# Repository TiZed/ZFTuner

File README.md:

# ZFTuner

A 100W automatic antenna tuner, utilizing latching relays.

This project is still work in progress...

CC BY-NC-SA 4.0 Deed\
https://creativecommons.org/licenses/by-nc-sa/4.0/

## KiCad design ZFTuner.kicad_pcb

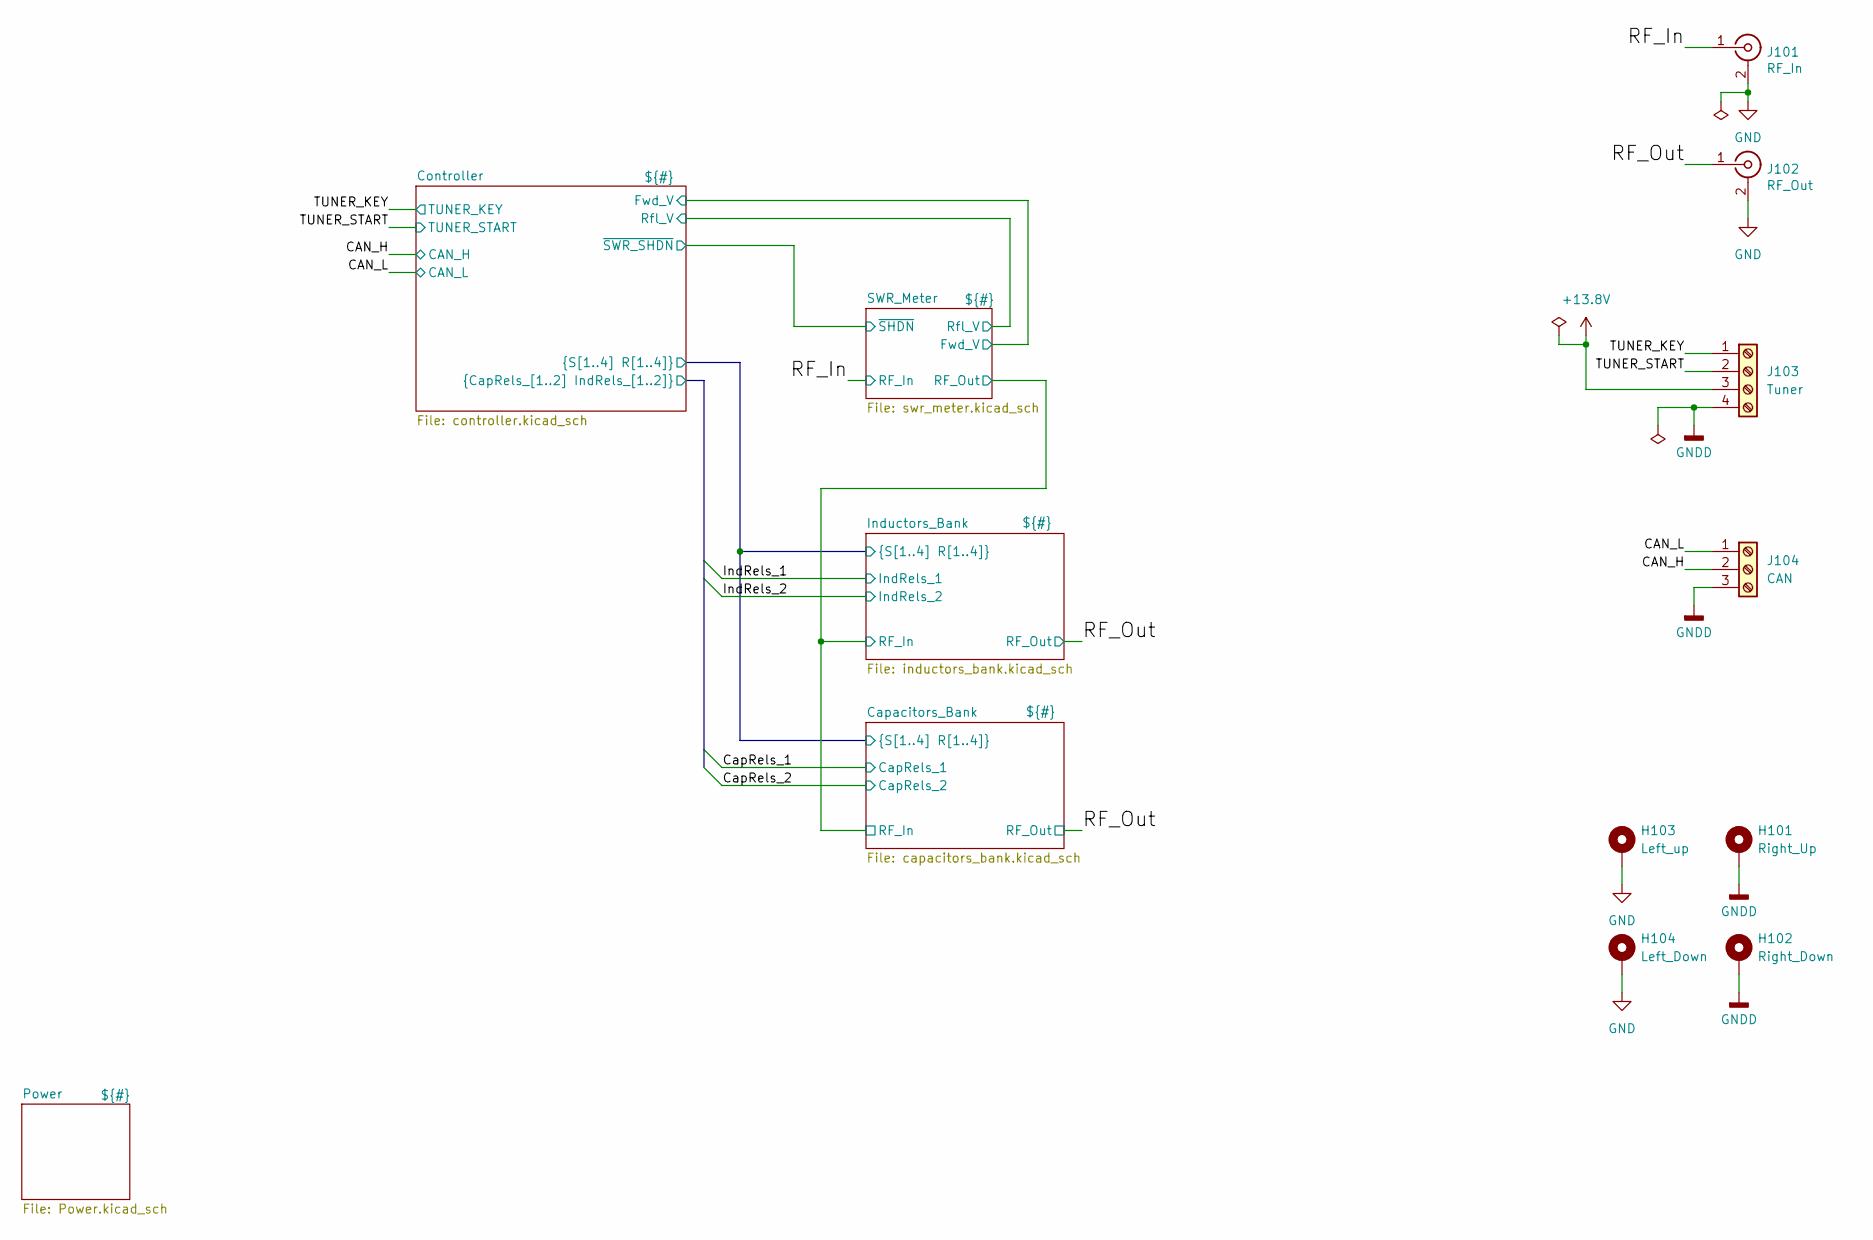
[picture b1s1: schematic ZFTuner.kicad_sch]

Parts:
H101: Right_Up; MountingHole_3.2mm_M3_ISO7380_Pad
H102: Right_Down; MountingHole_3.2mm_M3_ISO7380_Pad
H103: Left_up; MountingHole_3.2mm_M3_ISO7380_Pad
H104: Left_Down; MountingHole_3.2mm_M3_ISO7380_Pad
J101: RF_In; SMA_Bat_Wireless_BWSMA-KE-P001_EdgeMount_1.6mm-PCB
J102: RF_Out; SMA_Bat_Wireless_BWSMA-KE-P001_EdgeMount_1.6mm-PCB
J103: Tuner; TerminalBlock_Phoenix_PT-1,5-4-3.5-H_1x04_P3.50mm_Horizontal
J104: CAN; TerminalBlock_Phoenix_PT-1,5-3-3.5-H_1x03_P3.50mm_Horizontal

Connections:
+13.8V: J103.3; also elsewhere on the board
/CAN_H: J104.2; also elsewhere on the board
/CAN_L: J104.1; also elsewhere on the board
/RF_In: J101.1 (In); also elsewhere on the board
/RF_Out: J102.1 (In); also elsewhere on the board
/TUNER_KEY: J103.1; also elsewhere on the board
/TUNER_START: J103.2; also elsewhere on the board
GND: H103.1, H104.1, J101.2 (Ext), J102.2 (Ext); also elsewhere on the board
GNDD: H101.1, H102.1, J103.4, J104.3; also elsewhere on the board

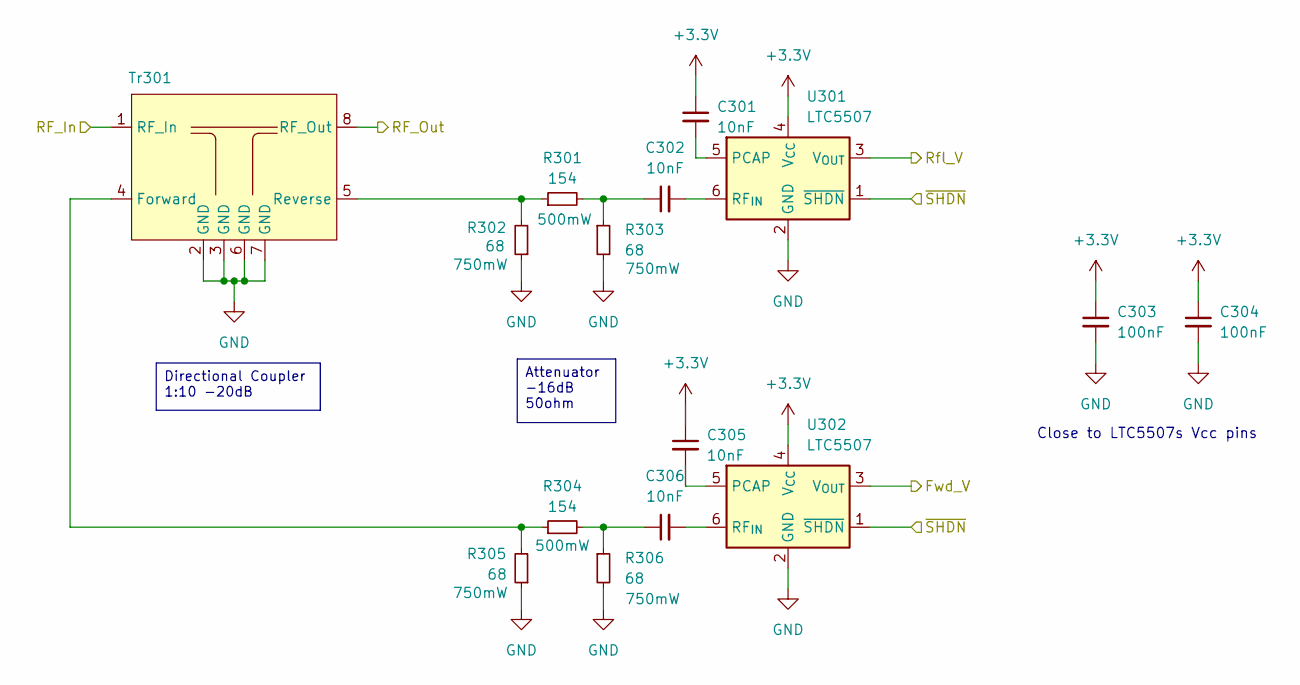
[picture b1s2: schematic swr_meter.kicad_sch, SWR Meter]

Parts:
C301, C302, C305, C306: 10nF; C_0603_1608Metric
C303, C304: 100nF; C_0603_1608Metric
R301, R304: 154; R_1210_3225Metric
R302, R303, R305, R306: 68; R_2010_5025Metric
Tr301: Direction_Coupler
U301, U302: LTC5507; TSOT-23-6

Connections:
+3.3V: C301.1, C303.1, C304.1, C305.1, U301.4 (V_{CC}), U302.4 (V_{CC}); also elsewhere on the board
/Capacitors_Bank/RF_In: Tr301.8 (RF_Out); also elsewhere on the board
/Controller/Fwd_V: U302.3 (V_{OUT}); also elsewhere on the board
/Controller/Rfl_V: U301.3 (V_{OUT}); also elsewhere on the board
/Controller/~SWR_SHDN: U301.1 (~SHDN), U302.1 (~SHDN); also elsewhere on the board
/RF_In: Tr301.1 (RF_In); also elsewhere on the board
GND: C303.2, C304.2, R302.1, R303.2, R305.1, R306.2, Tr301.2 (GND), Tr301.3 (GND), Tr301.6 (GND), Tr301.7 (GND), U301.2 (GND), U302.2 (GND); also elsewhere on the board
unnamed: C302.1, R301.2, R303.1
unnamed: C306.1, R304.2, R306.1
unnamed: R304.1, R305.2, Tr301.4 (Forward)
unnamed: R301.1, R302.2, Tr301.5 (Reverse)
unnamed: C301.2, U301.5 (PCAP)
unnamed: C302.2, U301.6 (RF_{IN})
unnamed: C305.2, U302.5 (PCAP)
unnamed: C306.2, U302.6 (RF_{IN})

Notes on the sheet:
Close to LTC5507s Vcc pins
Attenuator -16dB 50ohm
Directional Coupler 1:10 -20dB

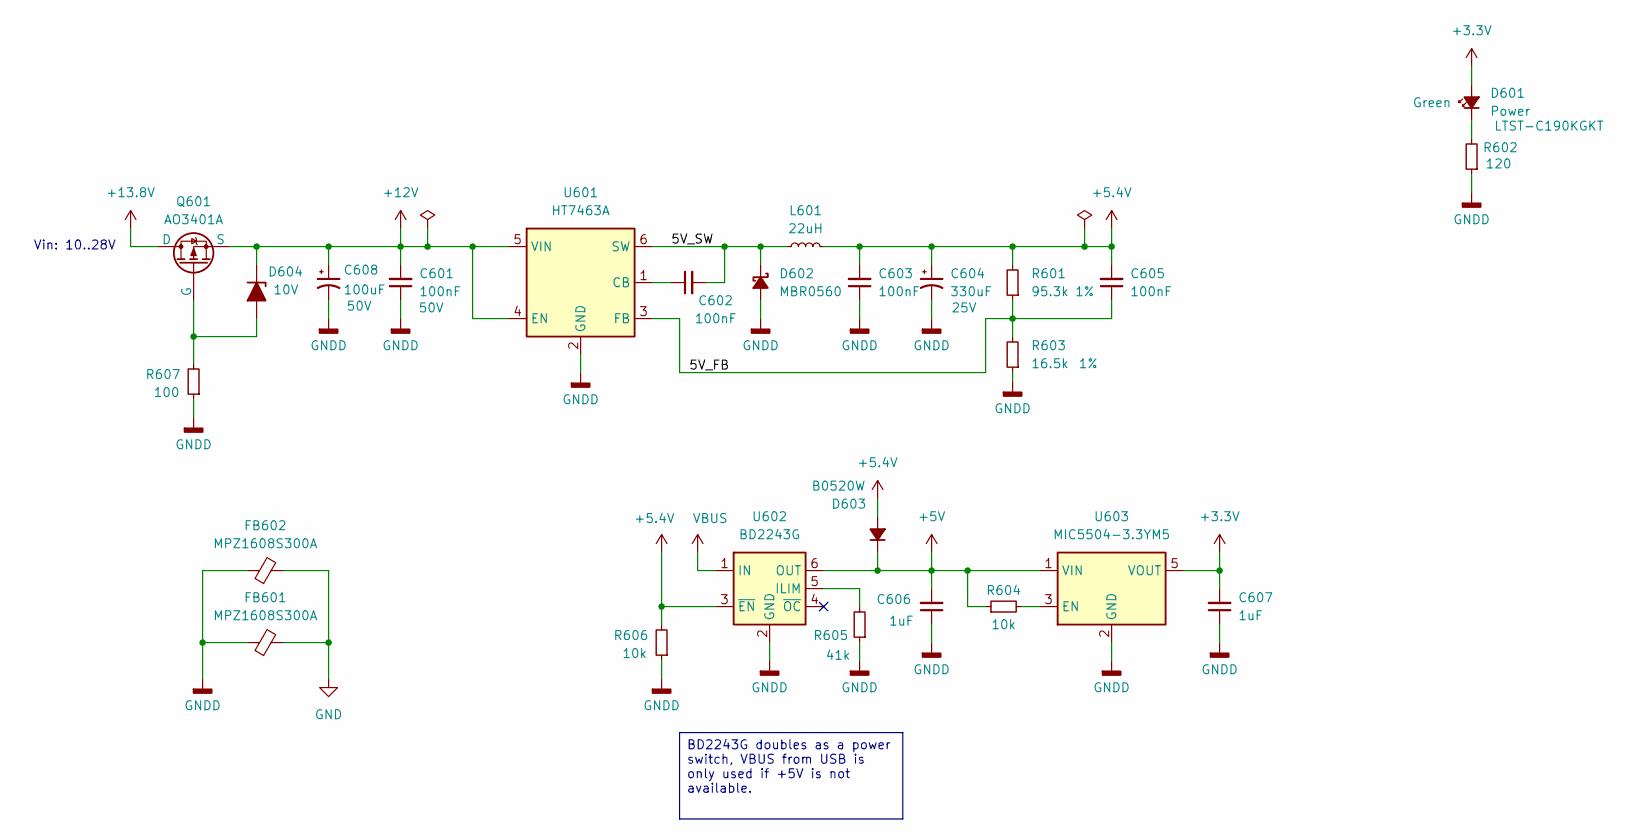
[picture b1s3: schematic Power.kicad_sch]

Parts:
C601: 100nF; C_0603_1608Metric; Voltage 50V
C602, C603, C605: 100nF; C_0603_1608Metric
C604: 330uF; CP_Elec_6.3x7.7; Voltage 25V; Partnumber 189RV0016
C606, C607: 1uF; C_0603_1608Metric
C608: 100uF; CP_Elec_8x10; Voltage 50V; Partnumber UUD1H101MNL1GS
D601: Power; LED_0603_1608Metric; Part LTST-C190KGKT
D602: MBR0560; D_SOD-123; Partnumber MBR0560
D603: B0520W; D_SOD-123
D604: 10V; D_SOD-123; Partnumber BZT52C10
FB601, FB602: MPZ1608S300A; L_0603_1608Metric
L601: 22uH; L_1210_3225Metric; Partnumber NLCV32T-220K-PF
Q601: AO3401A; SOT-23
R601: 95.3k; R_0603_1608Metric; Tolerance 1%
R602: 120; R_0603_1608Metric
R603: 16.5k; R_0603_1608Metric; Tolerance 1%
R604, R606: 10k; R_0603_1608Metric
R605: 41k; R_0603_1608Metric
R607: 100; R_0603_1608Metric
U601: HT7463A; SOT-23-6; Partnumber HT7463A
U602: BD2243G; TSOP-6_1.65x3.05mm_P0.95mm
U603: MIC5504-3.3YM5; SOT-23-5

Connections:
+3.3V: C607.2, D601.2 (A), U603.5 (VOUT); also elsewhere on the board
+5.4V: C603.2, C604.1, C605.2, D603.2 (A), L601.2, R601.2, R606.2, U602.3 (~EN)
+5V: C606.2, D603.1 (K), R604.1, U602.6 (OUT), U603.1 (VIN); also elsewhere on the board
+12V: C601.2, C608.1, D604.1 (K), Q601.3 (S), U601.4 (EN), U601.5 (VIN); also elsewhere on the board
+13.8V: Q601.1 (D); also elsewhere on the board
/Power/5V_FB: C605.1, R601.1, R603.2, U601.3 (FB)
/Power/5V_SW: C602.2, D602.1 (K), L601.1, U601.6 (SW)
GND: FB601.2, FB602.2; also elsewhere on the board
GNDD: C601.1, C603.1, C604.2, C606.1, C607.1, C608.2, D602.2 (A), FB601.1, FB602.1, R602.1, R603.1, R605.1, R606.1, R607.1, U601.2 (GND), U602.2 (GND), U603.2 (GND); also elsewhere on the board
unnamed: D601.1 (K), R602.2
unnamed: D604.2 (A), Q601.2 (G), R607.2
unnamed: C602.1, U601.1 (CB)
unnamed: R605.2, U602.5 (ILIM)
unnamed: R604.2, U603.3 (EN)
VBUS: U602.1 (IN); also elsewhere on the board

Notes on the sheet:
Vin: 10..28V
BD2243G doubles as a power switch, VBUS from USB is only used if +5V is not available.

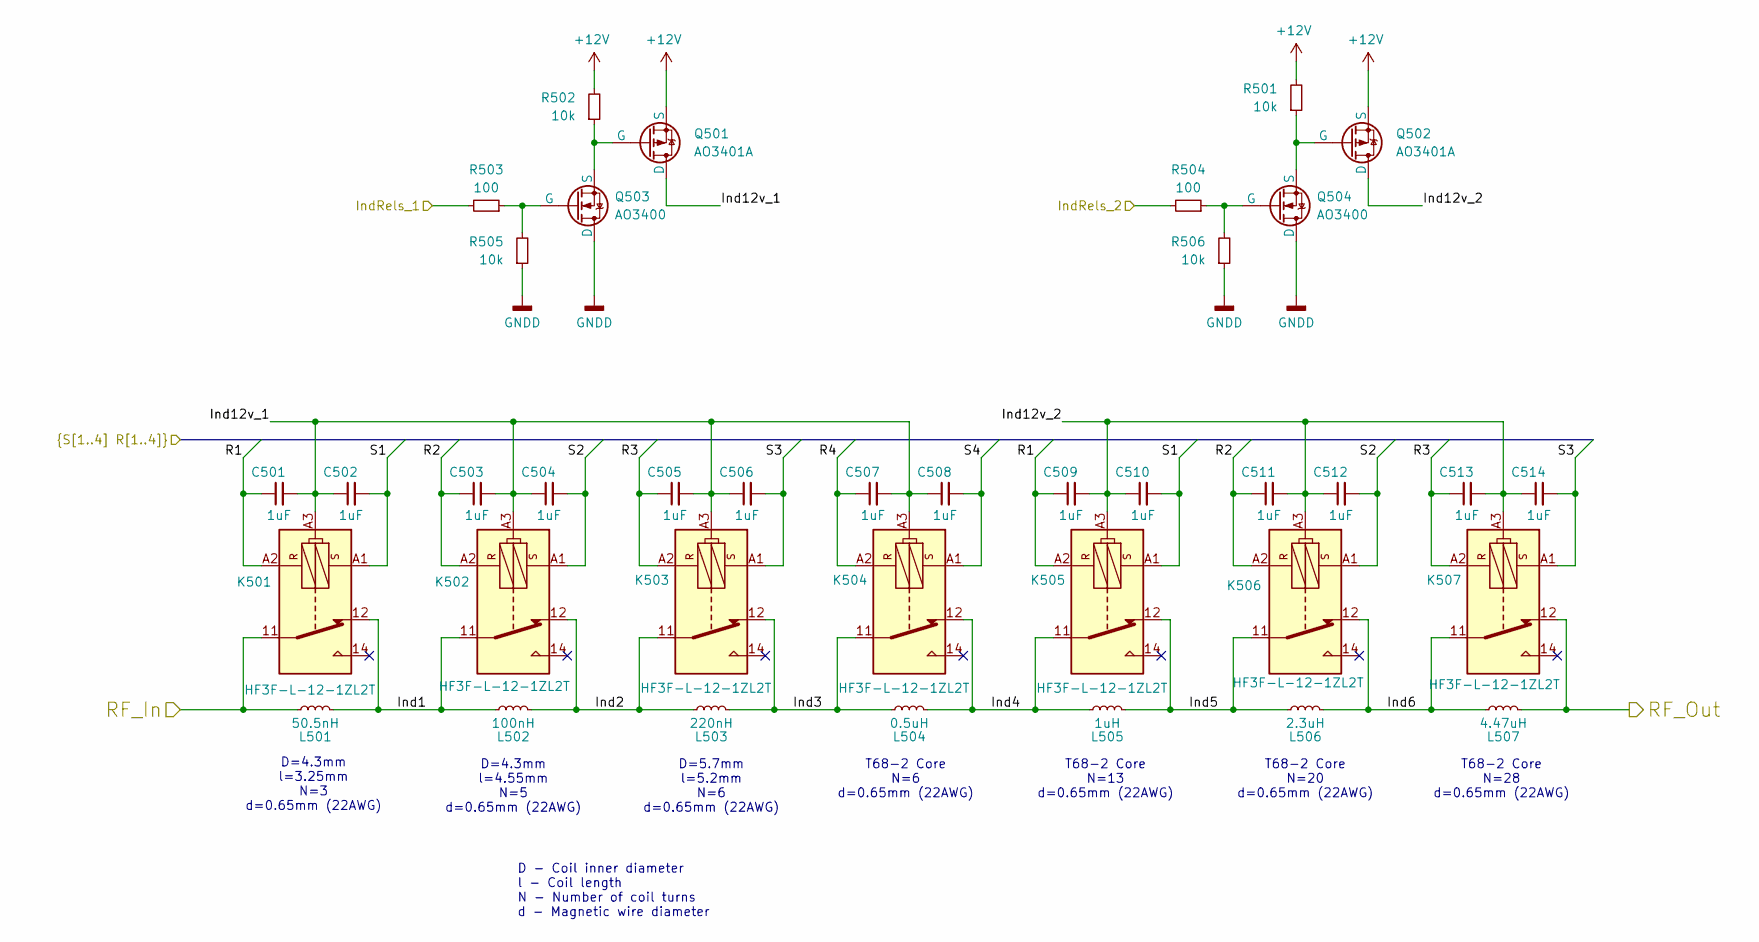
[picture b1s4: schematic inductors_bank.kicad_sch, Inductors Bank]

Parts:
C501, C502, C503, C504, C505, C506, C507, C508, C509, C510, C511, C512, C513, C514: 1uF; C_0603_1608Metric
K501, K502, K503, K504, K505, K506, K507: HF3F-L-12-1ZL2T; Relay_SPDT_Hongfa_HF3F-L-xx-1ZL2T
L501: 50.5nH; Inductor_3DP_N3_L5.35mm_W6.3mm_P2.58mm
L502: 100nH; Inductor_3DP_N5_L6.69mm_W6.3mm_P3.92mm
L503: 220nH; Inductor_3DP_N6_L7.36mm_W7.7mm_P4.59mm
L504: 0.5uH; Toroid_Vertical_L19.5mm_W8.0mm_P7.5mm
L505: 1uH; Toroid_Vertical_L19.5mm_W8.0mm_P7.5mm
L506: 2.3uH; Toroid_Vertical_L19.5mm_W8.0mm_P7.5mm
L507: 4.47uH; Toroid_Vertical_L19.5mm_W8.0mm_P7.5mm
Q501, Q502: AO3401A; SOT-23
Q503, Q504: AO3400; SOT-23
R501, R502, R505, R506: 10k; R_0603_1608Metric
R503, R504: 100; R_0603_1608Metric

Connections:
+12V: Q501.3 (S), Q502.3 (S), R501.2, R502.2; also elsewhere on the board
/Capacitors_Bank/R1: C501.1, C509.1, K501.A2, K505.A2; also elsewhere on the board
/Capacitors_Bank/R2: C503.1, C511.1, K502.A2, K506.A2; also elsewhere on the board
/Capacitors_Bank/R3: C505.1, C513.1, K503.A2, K507.A2; also elsewhere on the board
/Capacitors_Bank/R4: C507.1, K504.A2; also elsewhere on the board
/Capacitors_Bank/RF_In: K501.11, L501.1; also elsewhere on the board
/Capacitors_Bank/S1: C502.2, C510.2, K501.A1, K505.A1; also elsewhere on the board
/Capacitors_Bank/S2: C504.2, C512.2, K502.A1, K506.A1; also elsewhere on the board
/Capacitors_Bank/S3: C506.2, C514.2, K503.A1, K507.A1; also elsewhere on the board
/Capacitors_Bank/S4: C508.2, K504.A1; also elsewhere on the board
/Controller/IndRels_1: R503.2; also elsewhere on the board
/Controller/IndRels_2: R504.2; also elsewhere on the board
/Inductors_Bank/Ind1: K501.12, K502.11, L501.2, L502.1
/Inductors_Bank/Ind2: K502.12, K503.11, L502.2, L503.1
/Inductors_Bank/Ind3: K503.12, K504.11, L503.2, L504.1
/Inductors_Bank/Ind4: K504.12, K505.11, L504.2, L505.1
/Inductors_Bank/Ind5: K505.12, K506.11, L505.2, L506.1
/Inductors_Bank/Ind6: K506.12, K507.11, L506.2, L507.1
/Inductors_Bank/Ind12v_1: C501.2, C502.1, C503.2, C504.1, C505.2, C506.1, C507.2, C508.1, K501.A3, K502.A3, K503.A3, K504.A3, Q501.1 (D)
/Inductors_Bank/Ind12v_2: C509.2, C510.1, C511.2, C512.1, C513.2, C514.1, K505.A3, K506.A3, K507.A3, Q502.1 (D)
/RF_Out: K507.12, L507.2; also elsewhere on the board
GNDD: Q503.1 (D), Q504.1 (D), R505.1, R506.1; also elsewhere on the board
unnamed: Q501.2 (G), Q503.3 (S), R502.1
unnamed: Q502.2 (G), Q504.3 (S), R501.1
unnamed: Q503.2 (G), R503.1, R505.2
unnamed: Q504.2 (G), R504.1, R506.2

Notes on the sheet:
D=5.7mm l=5.2mm N=6 d=0.65mm (22AWG)
D=4.3mm l=4.55mm N=5 d=0.65mm (22AWG)
D=4.3mm l=3.25mm N=3 d=0.65mm (22AWG)
T68-2 Core N=6 d=0.65mm (22AWG)
D - Coil inner diameter l - Coil length N - Number of coil turns d - Magnetic wire diameter
T68-2 Core N=28 d=0.65mm (22AWG)
T68-2 Core N=20 d=0.65mm (22AWG)
T68-2 Core N=13 d=0.65mm (22AWG)

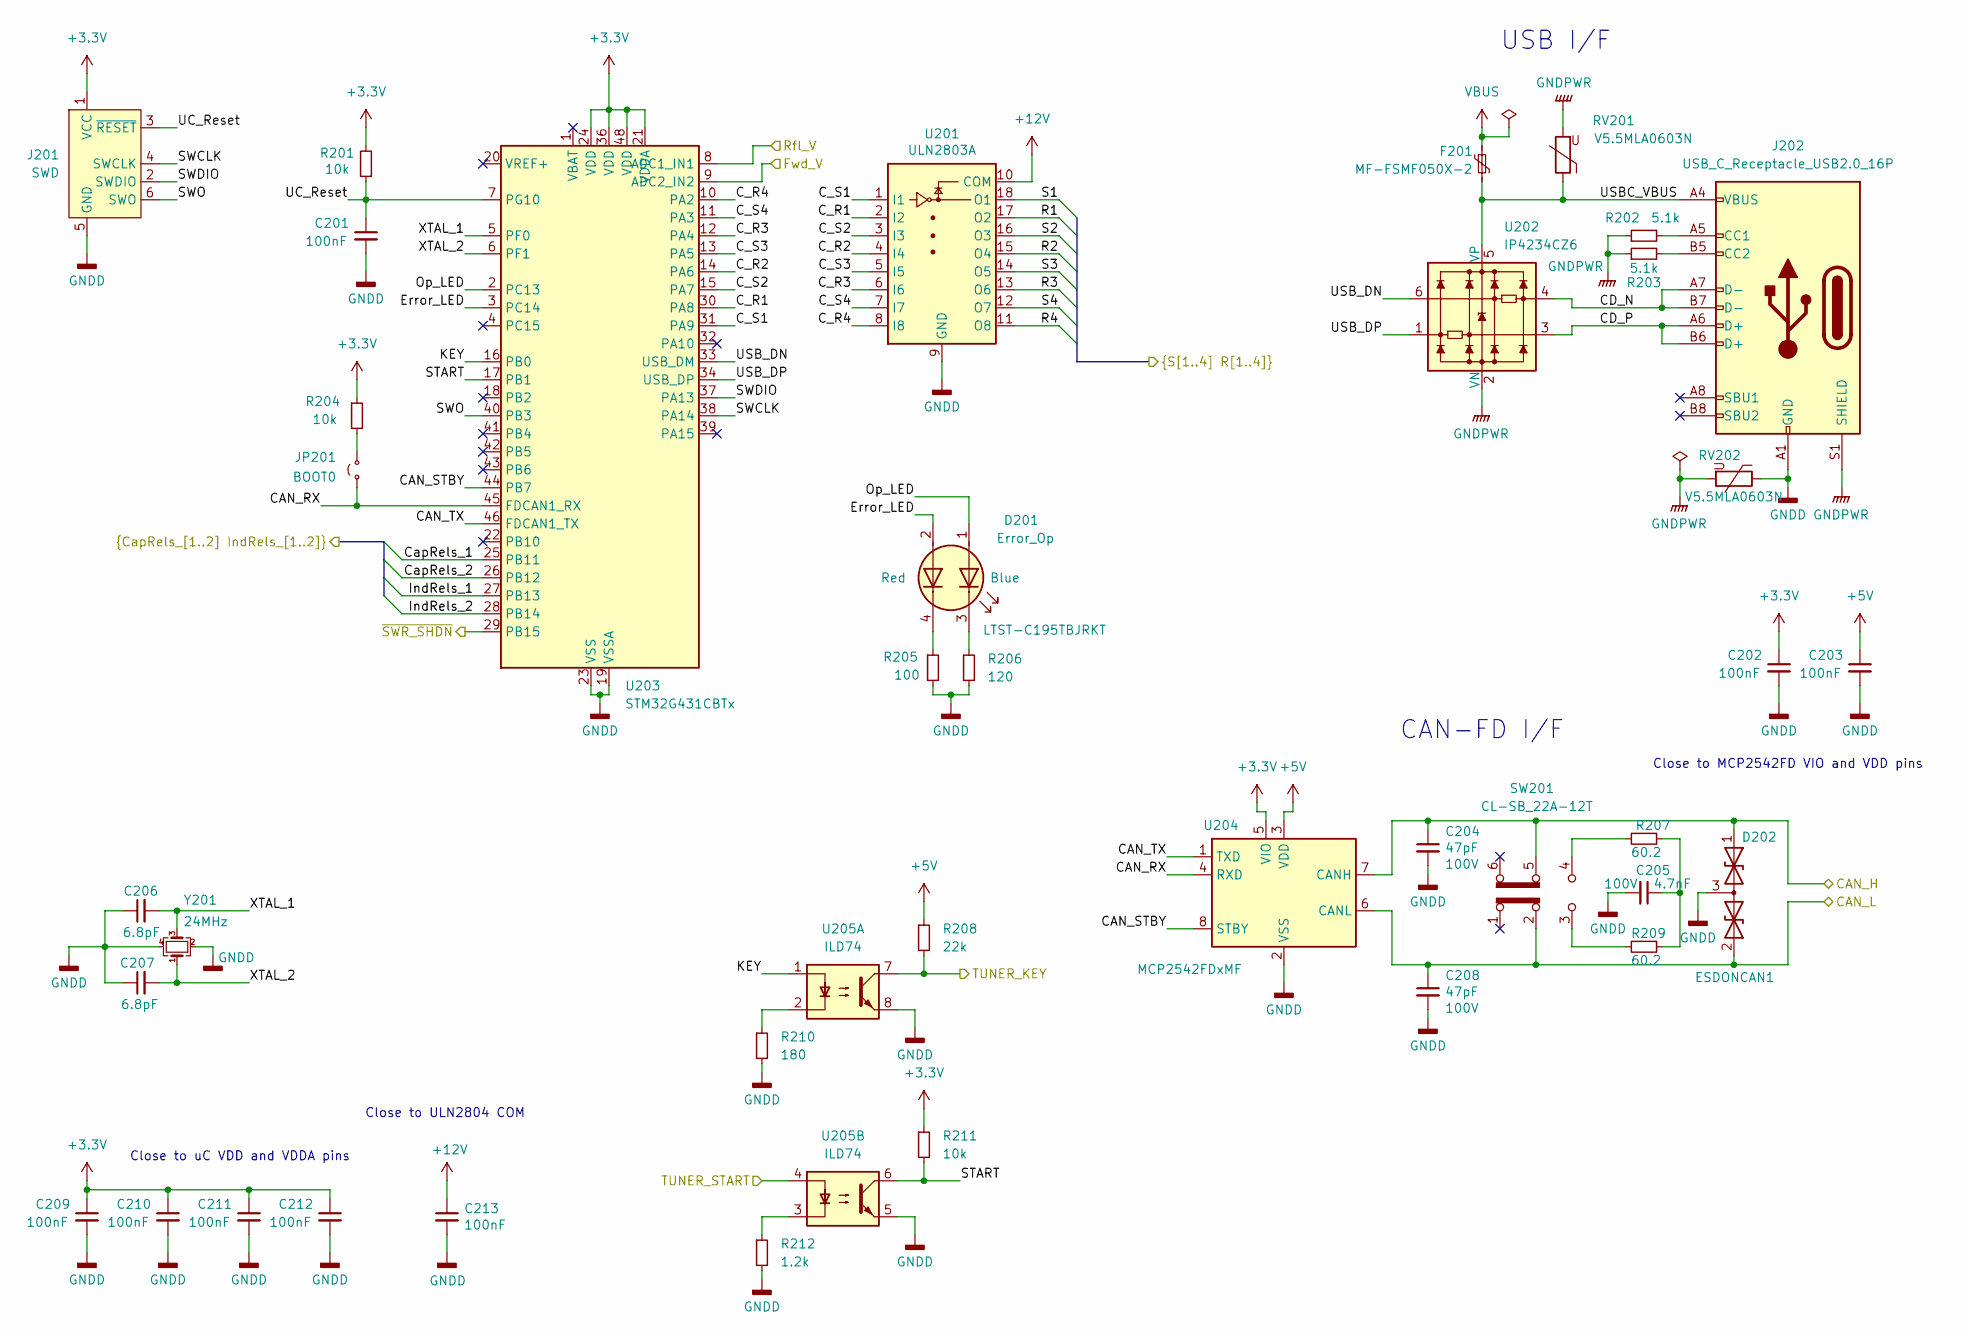
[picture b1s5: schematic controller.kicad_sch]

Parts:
C201, C202, C203, C209, C210, C211, C212, C213: 100nF; C_0603_1608Metric
C204, C208: 47pF; C_0603_1608Metric; Voltage 100V
C205: 4.7nF; C_0402_1005Metric; Voltage 100V
C206, C207: 6.8pF; C_0603_1608Metric
D201: Error_Op; LED_Dual_1615_1.6mm_1.5mm; Part LTST-C195TBJRKT
D202: ESDONCAN1; SOT-23
F201: MF-FSMF050X-2; Fuse_0603_1608Metric
J201: SWD; Tag-Connect_TC2030-IDC-NL_2x03_P1.27mm_Vertical
J202: USB_C_Receptacle_USB2.0_16P; USB_C_Receptacle_XKB_U262-16XN-4BVC11
JP201: BOOT0; PinHeader_1x02_P1.27mm_Vertical
R201, R204, R211: 10k; R_0603_1608Metric
R202, R203: 5.1k; R_0603_1608Metric
R205: 100; R_0603_1608Metric
R206: 120; R_0603_1608Metric
R207, R209: 60.2; R_1206_3216Metric
R208: 22k; R_0603_1608Metric
R210: 180; R_0603_1608Metric
R212: 1.2k; R_0603_1608Metric
RV201, RV202: V5.5MLA0603N; Fuse_0603_1608Metric
SW201: CL-SB_22A-12T; SW_Slide_DPDT_Nidec_CL-SB-22A
U201: ULN2803A; SOIC-18W_7.5x11.6mm_P1.27mm
U202: IP4234CZ6; SC-74-6_1.55x2.9mm_P0.95mm
U203: STM32G431CBTx; LQFP-48_7x7mm_P0.5mm
U204: MCP2542FDxMF; DFN-8-1EP_3x3mm_P0.65mm_EP1.55x2.4mm
U205: ILD74; SOP-8_3.9x4.9mm_P1.27mm
Y201: 24MHz; Crystal_SMD_3225-4Pin_3.2x2.5mm

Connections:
+3.3V: C202.1, C209.1, C210.1, C211.1, C212.1, J201.1 (VCC), R201.2, R204.1, R211.1, U203.21 (VDDA), U203.24 (VDD), U203.36 (VDD), U203.48 (VDD), U204.5 (VIO); also elsewhere on the board
+5V: C203.1, R208.1, U204.3 (VDD); also elsewhere on the board
+12V: C213.1, U201.10 (COM); also elsewhere on the board
/CAN_H: C204.1, D202.1 (A1), SW201.5 (B), U204.7 (CANH); also elsewhere on the board
/CAN_L: C208.1, D202.2 (A2), SW201.2 (B), U204.6 (CANL); also elsewhere on the board
/Capacitors_Bank/R1: U201.17 (O2); also elsewhere on the board
/Capacitors_Bank/R2: U201.15 (O4); also elsewhere on the board
/Capacitors_Bank/R3: U201.13 (O6); also elsewhere on the board
/Capacitors_Bank/R4: U201.11 (O8); also elsewhere on the board
/Capacitors_Bank/S1: U201.18 (O1); also elsewhere on the board
/Capacitors_Bank/S2: U201.16 (O3); also elsewhere on the board
/Capacitors_Bank/S3: U201.14 (O5); also elsewhere on the board
/Capacitors_Bank/S4: U201.12 (O7); also elsewhere on the board
/Controller/CAN_RX: JP201.1 (A), U203.45 (FDCAN1_RX), U204.4 (RXD)
/Controller/CAN_STBY: U203.44 (PB7), U204.8 (STBY)
/Controller/CAN_TX: U203.46 (FDCAN1_TX), U204.1 (TXD)
/Controller/CD_N: J202.A7 (D-), J202.B7 (D-), U202.4
/Controller/CD_P: J202.A6 (D+), J202.B6 (D+), U202.3
/Controller/C_R1: U201.2 (I2), U203.30 (PA8)
/Controller/C_R2: U201.4 (I4), U203.14 (PA6)
/Controller/C_R3: U201.6 (I6), U203.12 (PA4)
/Controller/C_R4: U201.8 (I8), U203.10 (PA2)
/Controller/C_S1: U201.1 (I1), U203.31 (PA9)
/Controller/C_S2: U201.3 (I3), U203.15 (PA7)
/Controller/C_S3: U201.5 (I5), U203.13 (PA5)
/Controller/C_S4: U201.7 (I7), U203.11 (PA3)
/Controller/CapRels_1: U203.25 (PB11); also elsewhere on the board
/Controller/CapRels_2: U203.26 (PB12); also elsewhere on the board
/Controller/Error_LED: D201.2 (A2), U203.3 (PC14)
/Controller/Fwd_V: U203.9 (ADC2_IN2); also elsewhere on the board
/Controller/IndRels_1: U203.27 (PB13); also elsewhere on the board
/Controller/IndRels_2: U203.28 (PB14); also elsewhere on the board
/Controller/KEY: U203.16 (PB0), U205.1
/Controller/Op_LED: D201.1 (A1), U203.2 (PC13)
/Controller/Rfl_V: U203.8 (ADC1_IN1); also elsewhere on the board
/Controller/START: R211.2, U203.17 (PB1), U205.6
/Controller/SWCLK: J201.4 (SWCLK), U203.38 (PA14)
/Controller/SWDIO: J201.2 (SWDIO), U203.37 (PA13)
/Controller/SWO: J201.6 (SWO), U203.40 (PB3)
/Controller/UC_Reset: C201.1, J201.3 (~RESET), R201.1, U203.7 (PG10)
/Controller/USBC_VBUS: F201.2, J202.A4 (VBUS), J202.A9 (VBUS), J202.B4 (VBUS), J202.B9 (VBUS), RV201.1, U202.5 (VP)
/Controller/USB_DN: U202.6, U203.33 (USB_DM)
/Controller/USB_DP: U202.1, U203.34 (USB_DP)
/Controller/XTAL_1: C206.2, U203.5 (PF0), Y201.3
/Controller/XTAL_2: C207.2, U203.6 (PF1), Y201.1
/Controller/~SWR_SHDN: U203.29 (PB15); also elsewhere on the board
/TUNER_KEY: R208.2, U205.7; also elsewhere on the board
/TUNER_START: U205.4; also elsewhere on the board
GNDD: C201.2, C202.2, C203.2, C204.2, C205.2, C206.1, C207.1, C208.2, C209.2, C210.2, C211.2, C212.2, C213.2, D202.3 (common), J201.5 (GND), J202.A1 (GND), J202.A12 (GND), J202.B1 (GND), J202.B12 (GND), R205.2, R206.2, R210.2, R212.2, RV202.1, U201.9 (GND), U203.19 (VSSA), U203.23 (VSS), U203.35 (VSS), U203.47 (VSS), U204.2 (VSS), U204.9 (VSS), U205.5, U205.8, Y201.2, Y201.4; also elsewhere on the board
GNDPWR: J202.S1 (SHIELD), R202.1, R203.1, RV201.2, RV202.2, U202.2 (VN)
unnamed: C205.1, R207.1, R209.1
unnamed: D201.3 (K1), R206.1
unnamed: D201.4 (K2), R205.1
unnamed: J202.A5 (CC1), R202.2
unnamed: J202.B5 (CC2), R203.2
unnamed: JP201.2 (B), R204.2
unnamed: R207.2, SW201.4 (A)
unnamed: R209.2, SW201.3 (C)
unnamed: R210.1, U205.2
unnamed: R212.1, U205.3
VBUS: F201.1; also elsewhere on the board

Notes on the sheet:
Close to uC VDD and VDDA pins
USB I/F
Close to MCP2542FD VIO and VDD pins
Close to ULN2804 COM
CAN-FD I/F

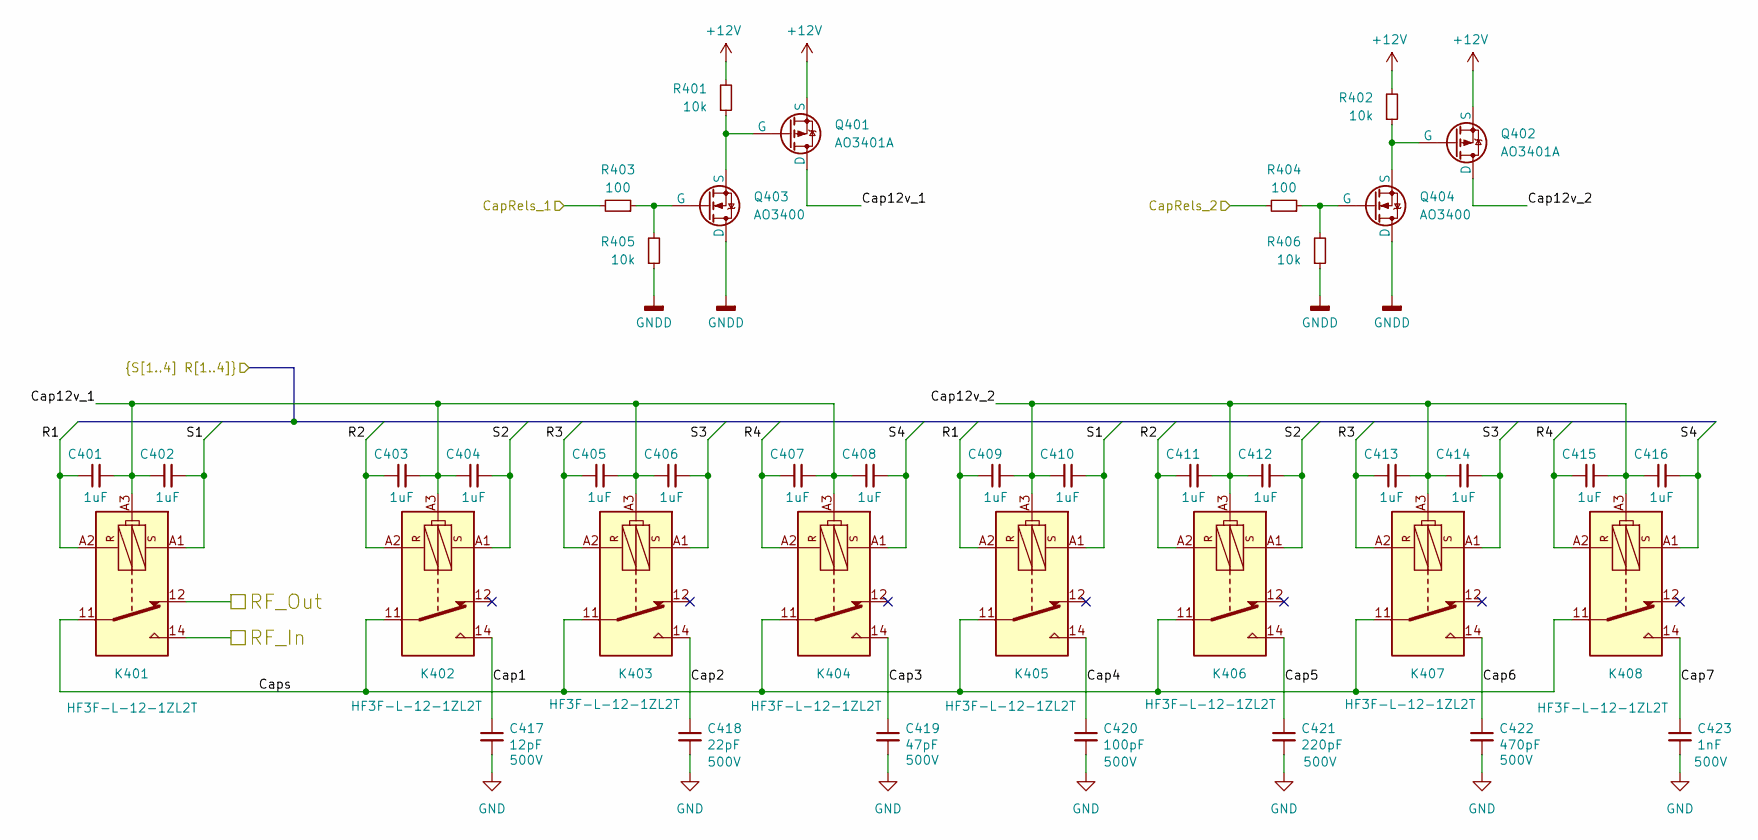
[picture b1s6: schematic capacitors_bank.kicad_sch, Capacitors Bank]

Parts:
C401, C402, C403, C404, C405, C406, C407, C408, C409, C410, C411, C412, C413, C414, C415, C416: 1uF; C_0603_1608Metric
C417: 12pF; C_1206_3216Metric; Voltage 500V
C418: 22pF; C_1206_3216Metric; Voltage 500V
C419: 47pF; C_1206_3216Metric; Voltage 500V
C420: 100pF; C_1206_3216Metric; Voltage 500V
C421: 220pF; C_1206_3216Metric; Voltage 500V
C422: 470pF; C_1206_3216Metric; Voltage 500V
C423: 1nF; C_1206_3216Metric; Voltage 500V
K401, K402, K403, K404, K405, K406, K407, K408: HF3F-L-12-1ZL2T; Relay_SPDT_Hongfa_HF3F-L-xx-1ZL2T
Q401, Q402: AO3401A; SOT-23
Q403, Q404: AO3400; SOT-23
R401, R402, R405, R406: 10k; R_0603_1608Metric
R403, R404: 100; R_0603_1608Metric

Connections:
+12V: Q401.3 (S), Q402.3 (S), R401.2, R402.2; also elsewhere on the board
/Capacitors_Bank/Cap1: C417.1, K402.14
/Capacitors_Bank/Cap2: C418.1, K403.14
/Capacitors_Bank/Cap3: C419.1, K404.14
/Capacitors_Bank/Cap4: C420.1, K405.14
/Capacitors_Bank/Cap5: C421.1, K406.14
/Capacitors_Bank/Cap6: C422.1, K407.14
/Capacitors_Bank/Cap7: C423.1, K408.14
/Capacitors_Bank/Cap12v_1: C401.2, C402.1, C403.2, C404.1, C405.2, C406.1, C407.2, C408.1, K401.A3, K402.A3, K403.A3, K404.A3, Q401.1 (D)
/Capacitors_Bank/Cap12v_2: C409.2, C410.1, C411.2, C412.1, C413.2, C414.1, C415.2, C416.1, K405.A3, K406.A3, K407.A3, K408.A3, Q402.1 (D)
/Capacitors_Bank/Caps: K401.11, K402.11, K403.11, K404.11, K405.11, K406.11, K407.11, K408.11
/Capacitors_Bank/R1: C401.1, C409.1, K401.A2, K405.A2; also elsewhere on the board
/Capacitors_Bank/R2: C403.1, C411.1, K402.A2, K406.A2; also elsewhere on the board
/Capacitors_Bank/R3: C405.1, C413.1, K403.A2, K407.A2; also elsewhere on the board
/Capacitors_Bank/R4: C407.1, C415.1, K404.A2, K408.A2; also elsewhere on the board
/Capacitors_Bank/RF_In: K401.14; also elsewhere on the board
/Capacitors_Bank/S1: C402.2, C410.2, K401.A1, K405.A1; also elsewhere on the board
/Capacitors_Bank/S2: C404.2, C412.2, K402.A1, K406.A1; also elsewhere on the board
/Capacitors_Bank/S3: C406.2, C414.2, K403.A1, K407.A1; also elsewhere on the board
/Capacitors_Bank/S4: C408.2, C416.2, K404.A1, K408.A1; also elsewhere on the board
/Controller/CapRels_1: R403.2; also elsewhere on the board
/Controller/CapRels_2: R404.2; also elsewhere on the board
/RF_Out: K401.12; also elsewhere on the board
GND: C417.2, C418.2, C419.2, C420.2, C421.2, C422.2, C423.2; also elsewhere on the board
GNDD: Q403.1 (D), Q404.1 (D), R405.1, R406.1; also elsewhere on the board
unnamed: Q401.2 (G), Q403.3 (S), R401.1
unnamed: Q402.2 (G), Q404.3 (S), R402.1
unnamed: Q403.2 (G), R403.1, R405.2
unnamed: Q404.2 (G), R404.1, R406.2

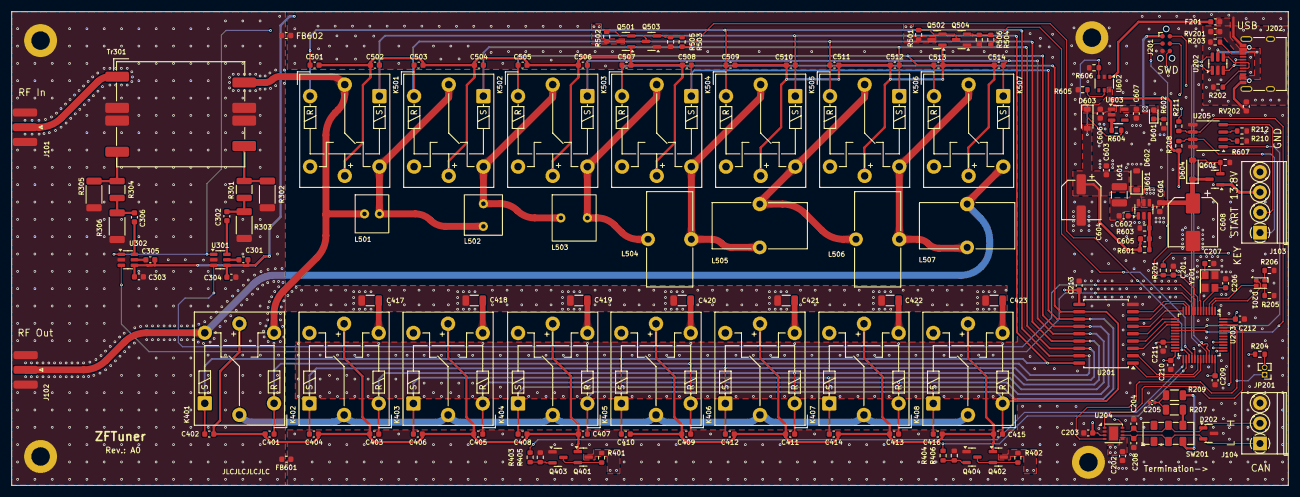
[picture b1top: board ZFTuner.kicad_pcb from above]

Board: 4 copper layers, 221.0 x 82.0 mm, 168 parts (0 on the bottom side), 108 nets.

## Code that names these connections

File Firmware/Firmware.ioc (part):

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Mcu.Name=STM32G431C(6-8-B)Tx
Mcu.Package=LQFP48
Mcu.UserName=STM32G431CBTx
PA0.GPIOParameters=GPIO_Label
PA0.GPIO_Label=Rfl_V
PA0.Mode=IN1-Single-Ended
PA0.Signal=ADC1_IN1
PA1.GPIOParameters=GPIO_Label
PA1.GPIO_Label=Fwd_V
PA1.Mode=IN2-Single-Ended
PA1.Signal=ADC1_IN2
PA11.Mode=Device
PA11.Signal=USB_DM
PA12.Mode=Device
PA12.Signal=USB_DP
PA13.Mode=Trace_Asynchronous_SW
PA13.Signal=SYS_JTMS-SWDIO
PA14.Mode=Trace_Asynchronous_SW
PA14.Signal=SYS_JTCK-SWCLK
PA2.GPIOParameters=GPIO_Speed,GPIO_Label
PA2.GPIO_Label=Relays_R4
PA2.GPIO_Speed=GPIO_SPEED_FREQ_LOW
PA2.Signal=GPIO_Output
PA3.GPIOParameters=GPIO_Label
PA3.GPIO_Label=Relays_S4
PA3.Signal=GPIO_Output
PA4.GPIOParameters=GPIO_Label
PA4.GPIO_Label=Relays_R3
PA4.Signal=GPIO_Output
PA5.GPIOParameters=GPIO_Label
PA5.GPIO_Label=Relays_S3
PA5.Signal=GPIO_Output
PA6.GPIOParameters=GPIO_Label
PA6.GPIO_Label=Relays_R2
PA6.Signal=GPIO_Output
PA7.GPIOParameters=GPIO_Label
PA7.GPIO_Label=Relays_S2
PA7.Signal=GPIO_Output
PA8.GPIOParameters=GPIO_Label
PA8.GPIO_Label=Relays_R1
PA8.Signal=GPIO_Output
PA9.GPIOParameters=GPIO_Label
PA9.GPIO_Label=Relays_S1
PA9.Signal=GPIO_Output
PB0.GPIOParameters=GPIO_Label
PB0.GPIO_Label=KEY
PB0.Signal=GPIO_Output
PB1.GPIOParameters=GPIO_Label,GPIO_ModeDefaultEXTI
PB1.GPIO_Label=START
PB1.GPIO_ModeDefaultEXTI=GPIO_MODE_IT_FALLING
PB1.Signal=GPXTI1
PB11.GPIOParameters=GPIO_Label
PB11.GPIO_Label=CapRels_1
PB11.Signal=GPIO_Output
PB12.GPIOParameters=GPIO_Label
PB12.GPIO_Label=CapRels_2
PB12.Signal=GPIO_Output
PB13.GPIOParameters=GPIO_Label
PB13.GPIO_Label=IndRels_1
PB13.Signal=GPIO_Output
PB14.GPIOParameters=GPIO_Label
PB14.GPIO_Label=IndRels_2
PB14.Signal=GPIO_Output
PB15.GPIOParameters=GPIO_Label
PB15.GPIO_Label=SWR_SHDN
PB15.Signal=GPIO_Output
PB3.Mode=Trace_Asynchronous_SW
PB3.Signal=SYS_JTDO-SWO
PB7.GPIOParameters=GPIO_Label
PB7.GPIO_Label=CAN_STBY
PB7.Signal=GPIO_Output
PB8-BOOT0.Mode=FDCAN_Activate
PB8-BOOT0.Signal=FDCAN1_RX
PB9.Mode=FDCAN_Activate
PB9.Signal=FDCAN1_TX
PC13.GPIOParameters=GPIO_Label
PC13.GPIO_Label=Op_LED
PC13.Signal=GPIO_Output
PC14-OSC32_IN.GPIOParameters=GPIO_Label
PC14-OSC32_IN.GPIO_Label=Error_LED
PC14-OSC32_IN.Signal=GPIO_Output
PF0-OSC_IN.Mode=HSE-External-Oscillator
PF0-OSC_IN.Signal=RCC_OSC_IN
PF1-OSC_OUT.Mode=HSE-External-Oscillator
PF1-OSC_OUT.Signal=RCC_OSC_OUT
RCC.HSE_VALUE=24000000
RCC.SYSCLKFreq_VALUE=144000000
RCC.SYSCLKSource=RCC_SYSCLKSOURCE_PLLCLK
board=custom

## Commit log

2024-03-23 First commit, schematic mostly done
2024-04-04 Add some missing footprints and rearranged schematics a bit
2024-04-04 Added comments for inductors structure
2024-04-04 3D printable coil forms with parametric CAD file
2024-04-04 Added README
2024-04-14 Fixed 3D printed air inductors dimensions
2024-04-14 more files for git to ignore
2024-04-14 Inductors footprints
2024-04-14 Set footprints for inductors. Improved schematic of capcitors and inductors banks.
2024-04-14 Added connectors to top schematic. Added xtal and optocouplers to controller.
2024-04-14 Updated all pins in STM32CubeMX project
2024-04-14 Added 'Power', 'Op' and 'Error' LEDs
2024-04-14 Added ADC configuration to FW
2024-04-14 Created PDF of schematic
2024-04-14 Added LEDs part numbers
2024-04-15 Start layout
2024-04-17 Placement of most components done
2024-04-20 Added missing silkscreen frame for 3DP inductors
2024-04-20 PCB layout nearly done
2024-04-20 Schematic fixes for PCB layout
2024-04-21 Everything is connected
2024-04-23 Adjusted some traces
2024-04-23 Updated schematic PDF
2024-04-24 Some pictures of the board
2024-04-24 Many more vias, improved some routing
2024-04-25 Some schematic cleanup and minor fixes
2024-04-25 More layout polishing
2024-04-25 Initial code generated
2024-04-26 Removed unclear text in schematic. Some minor PCB routing improvments. Added name and revision silkscreen
2024-04-27 Replaced SMA footprints with correct connectors
2024-04-28 Improved grounding
2024-04-29 Improve RF routing
2024-04-29 Readded some vias and fixed board dimensions
2024-04-29 Added transistors parts. Added reverse polarity protection, pending adding to layout
2024-05-02 Finshed and added revers polarity protection. Improved layout.
2024-05-02 Fixed 5.4V zone geometry
2024-05-03 Re-stiched GNDD vias. Added mounting holes.
2024-05-03 Minor schematic fixes
2024-05-03 Minor layout improvements
2024-05-04 Finished layout
2024-05-04 Fixed directional couler footprint. Improved RF In/Out SMA placement.
2024-05-04 Generated prodcution files
2024-05-04 Generated production files for directional coupler PCB
2024-05-05 Minor slikscreen fixes and direction coupler prodcution files
2024-05-10 Updated CubeMX
2024-05-13 Added relays control code and LTC5507 formula
2024-05-14 Started some CAN code
2024-06-07 Minor vias fixes
2024-07-06 Adapted direction coupler board for JLPCB 2-layer process
2025-08-20 A0 Production. Updated to KiCad 9.0.x
